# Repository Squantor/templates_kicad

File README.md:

# kicad_templates
Kicad templates that I use regularly
## checkout notes
This repository contains a few submodules, so after checking out do not forget to also check out the submodules.
```
git clone https://github.com/Squantor/LPC-breakout-boards.git
git submodule init
git submodule update
```
Submodules are my private kicad library that are used in my projects. I do try to use the kicad components as much as possible but for certain component types they are less then optimal or they do not exist.

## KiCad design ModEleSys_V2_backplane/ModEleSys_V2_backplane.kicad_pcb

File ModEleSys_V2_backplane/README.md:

# 10 by 10 cm aluminium box backplane
10 by 10 cm aluminium box backplane  capable of fitting 4 5*4cm modules
## TODO's
Still some things need to be done:
* Fill in this project description
* schematic entry 
* PCB layout
* Review with one night in between
* Production
* Assemble
* Test & characterise
* update Readme.md with pictures and BOM
## BOM
This is a list of hardware components. If just mentioned a generic component like a 1K 0402 resistor, just name it as such, free to substitute. If you need some special integrated IC's show some sources like Mouser, Digikey, Farnell, or LCSC
* Search on ebay/aliexpress for a 10 by 10 by 5 extruded aluminium box.
* Generic resistor in 0402 housing with a value
* Generic capacitor in 0603 housing with a value
* Special IC from [LCSC](https://lcsc.com/)
## Pictures

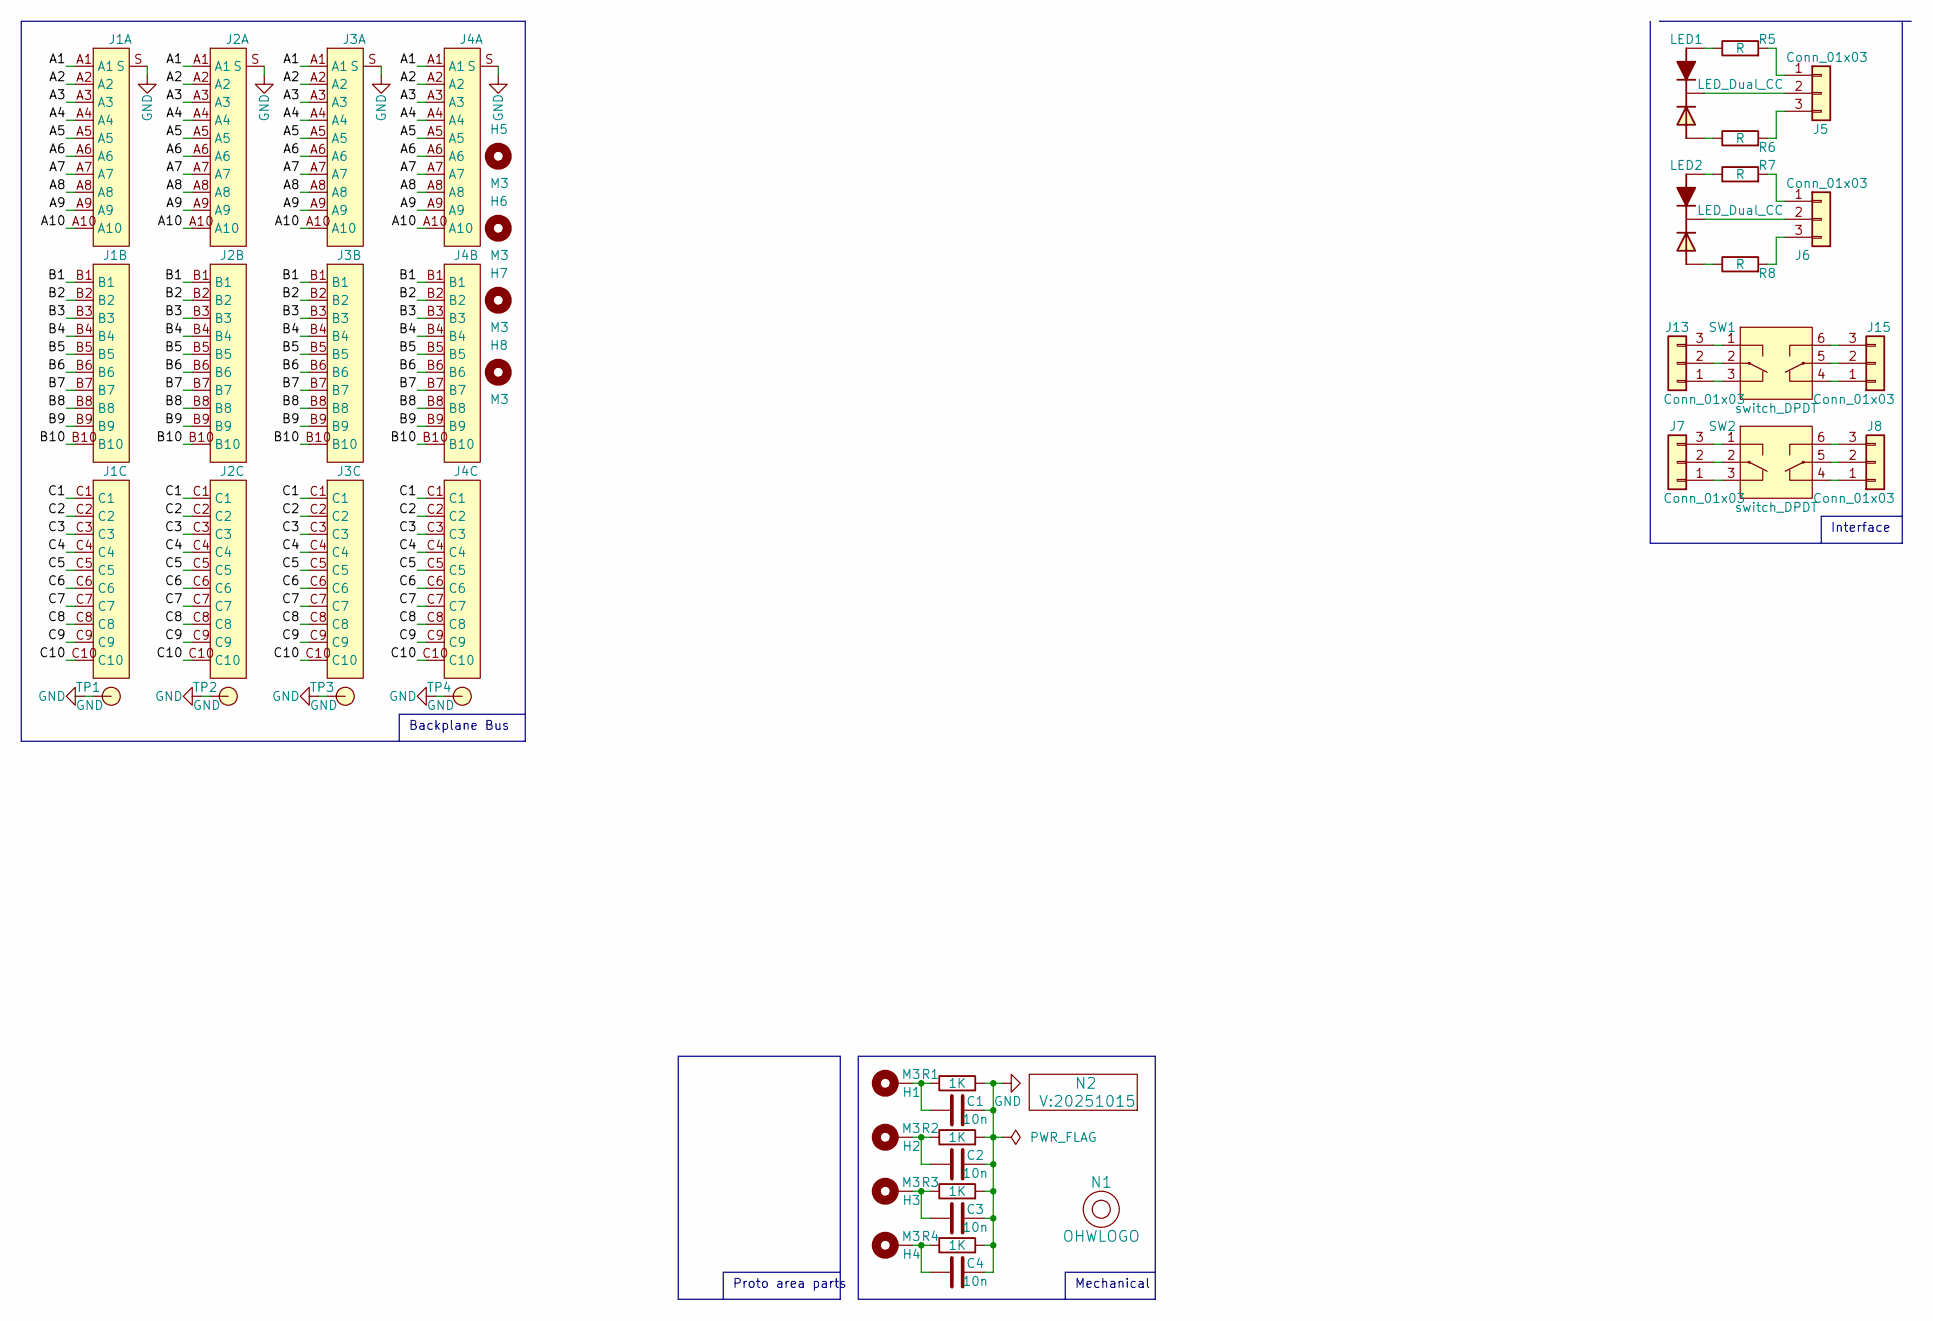
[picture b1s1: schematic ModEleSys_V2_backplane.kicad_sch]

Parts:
C1, C2, C3, C4: 10n; C_0805+0603
H1, H2, H3, H4, H5, H6, H7, H8: M3; MountingHole_3.2mm_M3_Pad_Via
J1, J2, J3, J4: DIN41612_C3_3x10_Female_Vertical_THT_shields
J5, J6, J7, J8, J13, J15: Conn_01x03; JST_PH_B3B-PH-K_1x03_P2.00mm_Vertical
LED1, LED2: LED_Dual_CC; LED_DUAL_TH245_90deg
N1: OHWLOGO; OSHW-Symbol_6.7x6mm_SilkScreen
N2: V:20251015; Label_Generic
R1, R2, R3, R4: 1K; R_0805+0603
R5, R6, R7, R8: R; R_0603_hand
SW1, SW2: switch_DPDT; PS-22F02
TP1, TP2, TP3, TP4: GND; TestPoint_hole_H05R10

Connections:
/A1: J1.A1, J2.A1, J3.A1, J4.A1
/A2: J1.A2, J2.A2, J3.A2, J4.A2
/A3: J1.A3, J2.A3, J3.A3, J4.A3
/A4: J1.A4, J2.A4, J3.A4, J4.A4
/A5: J1.A5, J2.A5, J3.A5, J4.A5
/A6: J1.A6, J2.A6, J3.A6, J4.A6
/A7: J1.A7, J2.A7, J3.A7, J4.A7
/A8: J1.A8, J2.A8, J3.A8, J4.A8
/A9: J1.A9, J2.A9, J3.A9, J4.A9
/A10: J1.A10, J2.A10, J3.A10, J4.A10
/B1: J1.B1, J2.B1, J3.B1, J4.B1
/B2: J1.B2, J2.B2, J3.B2, J4.B2
/B3: J1.B3, J2.B3, J3.B3, J4.B3
/B4: J1.B4, J2.B4, J3.B4, J4.B4
/B5: J1.B5, J2.B5, J3.B5, J4.B5
/B6: J1.B6, J2.B6, J3.B6, J4.B6
/B7: J1.B7, J2.B7, J3.B7, J4.B7
/B8: J1.B8, J2.B8, J3.B8, J4.B8
/B9: J1.B9, J2.B9, J3.B9, J4.B9
/B10: J1.B10, J2.B10, J3.B10, J4.B10
/C1: J1.C1, J2.C1, J3.C1, J4.C1
/C2: J1.C2, J2.C2, J3.C2, J4.C2
/C3: J1.C3, J2.C3, J3.C3, J4.C3
/C4: J1.C4, J2.C4, J3.C4, J4.C4
/C5: J1.C5, J2.C5, J3.C5, J4.C5
/C6: J1.C6, J2.C6, J3.C6, J4.C6
/C7: J1.C7, J2.C7, J3.C7, J4.C7
/C8: J1.C8, J2.C8, J3.C8, J4.C8
/C9: J1.C9, J2.C9, J3.C9, J4.C9
/C10: J1.C10, J2.C10, J3.C10, J4.C10
GND: C1.2, C2.2, C3.2, C4.2, J1.S, J2.S, J3.S, J4.S, R1.2, R2.2, R3.2, R4.2, TP1.1, TP2.1, TP3.1, TP4.1
unnamed: C1.1, H1.1, R1.1
unnamed: C2.1, H2.1, R2.1
unnamed: C3.1, H3.1, R3.1
unnamed: C4.1, H4.1, R4.1
unnamed: J5.1, R5.2
unnamed: J5.2, LED1.2 (C)
unnamed: J5.3, R6.2
unnamed: J6.1, R7.2
unnamed: J6.2, LED2.2 (C)
unnamed: J6.3, R8.2
unnamed: J7.1, SW2.3 (SW1_P2)
unnamed: J7.2, SW2.2 (SW1_C1)
unnamed: J7.3, SW2.1 (SW1_P1)
unnamed: J8.1, SW2.4 (SW2_P2)
unnamed: J8.2, SW2.5 (SW2_C1)
unnamed: J8.3, SW2.6 (SW2_P2)
unnamed: J13.1, SW1.3 (SW1_P2)
unnamed: J13.2, SW1.2 (SW1_C1)
unnamed: J13.3, SW1.1 (SW1_P1)
unnamed: J15.1, SW1.4 (SW2_P2)
unnamed: J15.2, SW1.5 (SW2_C1)
unnamed: J15.3, SW1.6 (SW2_P2)
unnamed: LED1.1 (A1), R5.1
unnamed: LED1.3 (A2), R6.1
unnamed: LED2.1 (A1), R7.1
unnamed: LED2.3 (A2), R8.1

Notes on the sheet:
Proto area parts
Mechanical
Interface
Backplane Bus

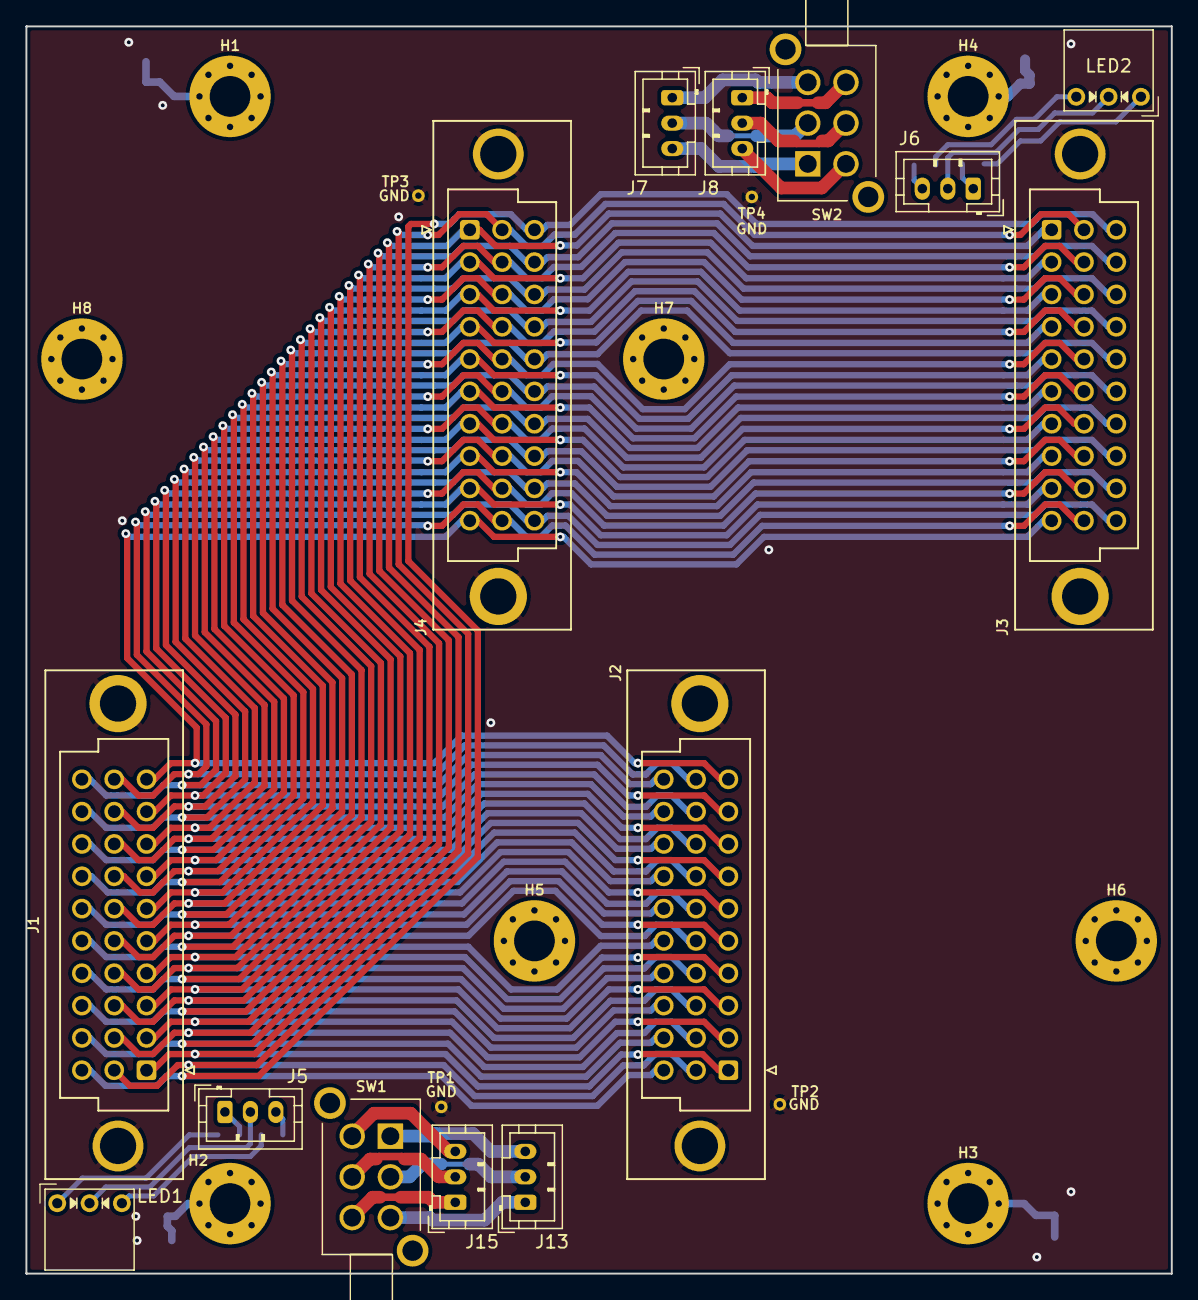
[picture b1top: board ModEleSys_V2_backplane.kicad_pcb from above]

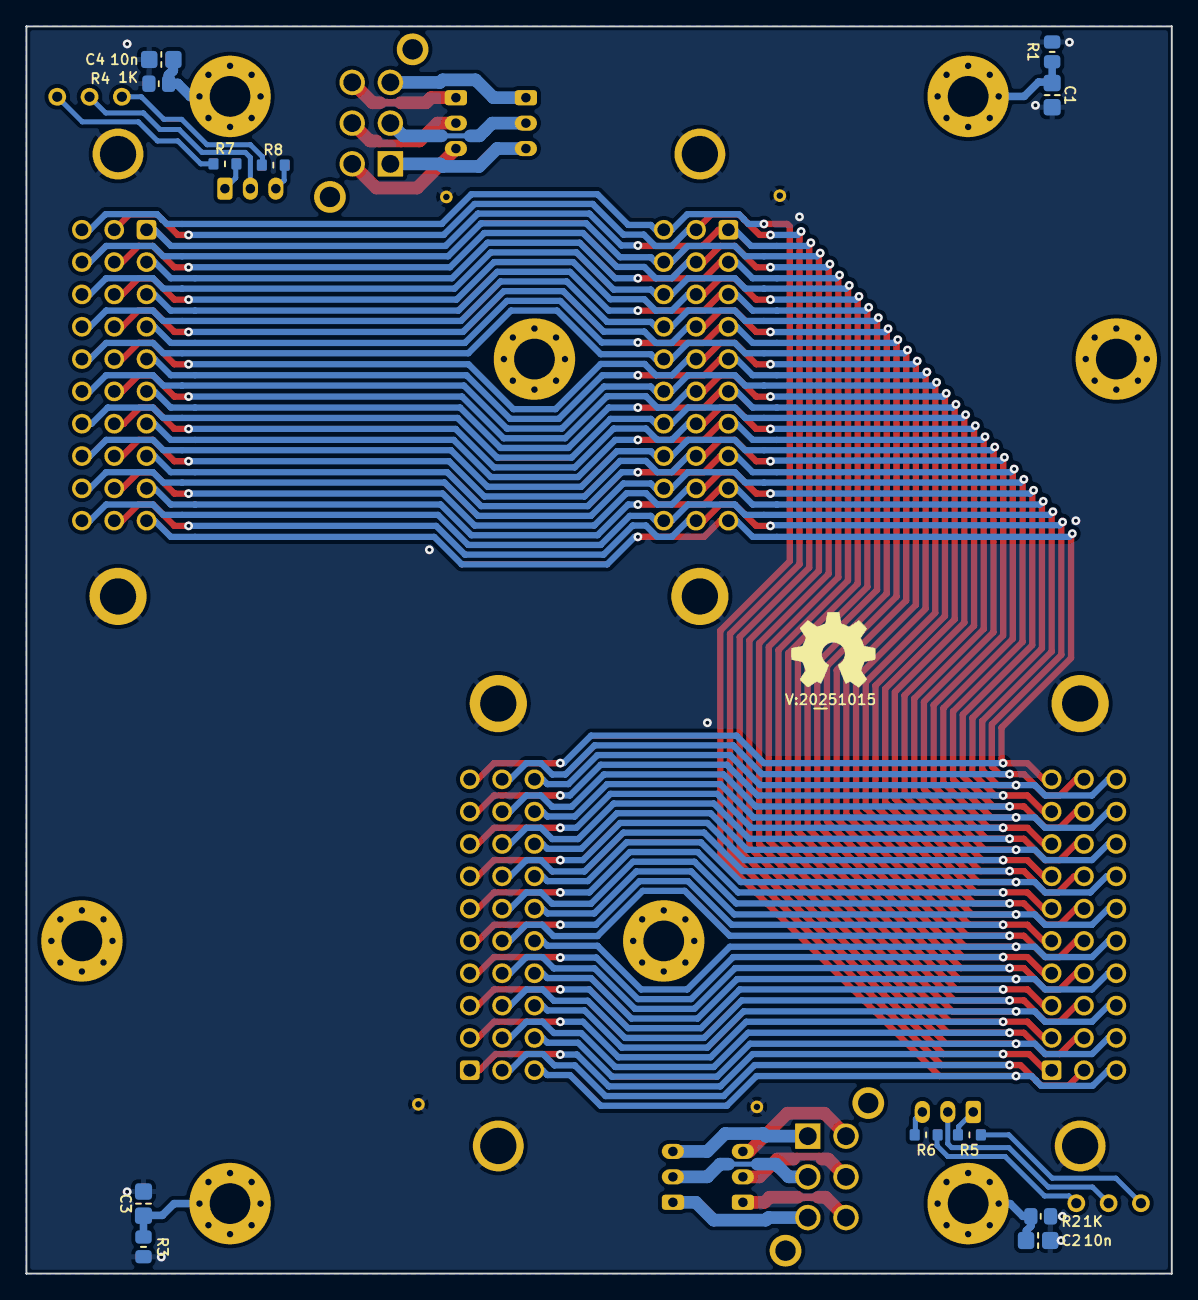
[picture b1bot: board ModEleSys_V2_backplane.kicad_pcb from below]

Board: 2 copper layers, 90.0 x 98.0 mm, 40 parts (14 on the bottom side), 57 nets.

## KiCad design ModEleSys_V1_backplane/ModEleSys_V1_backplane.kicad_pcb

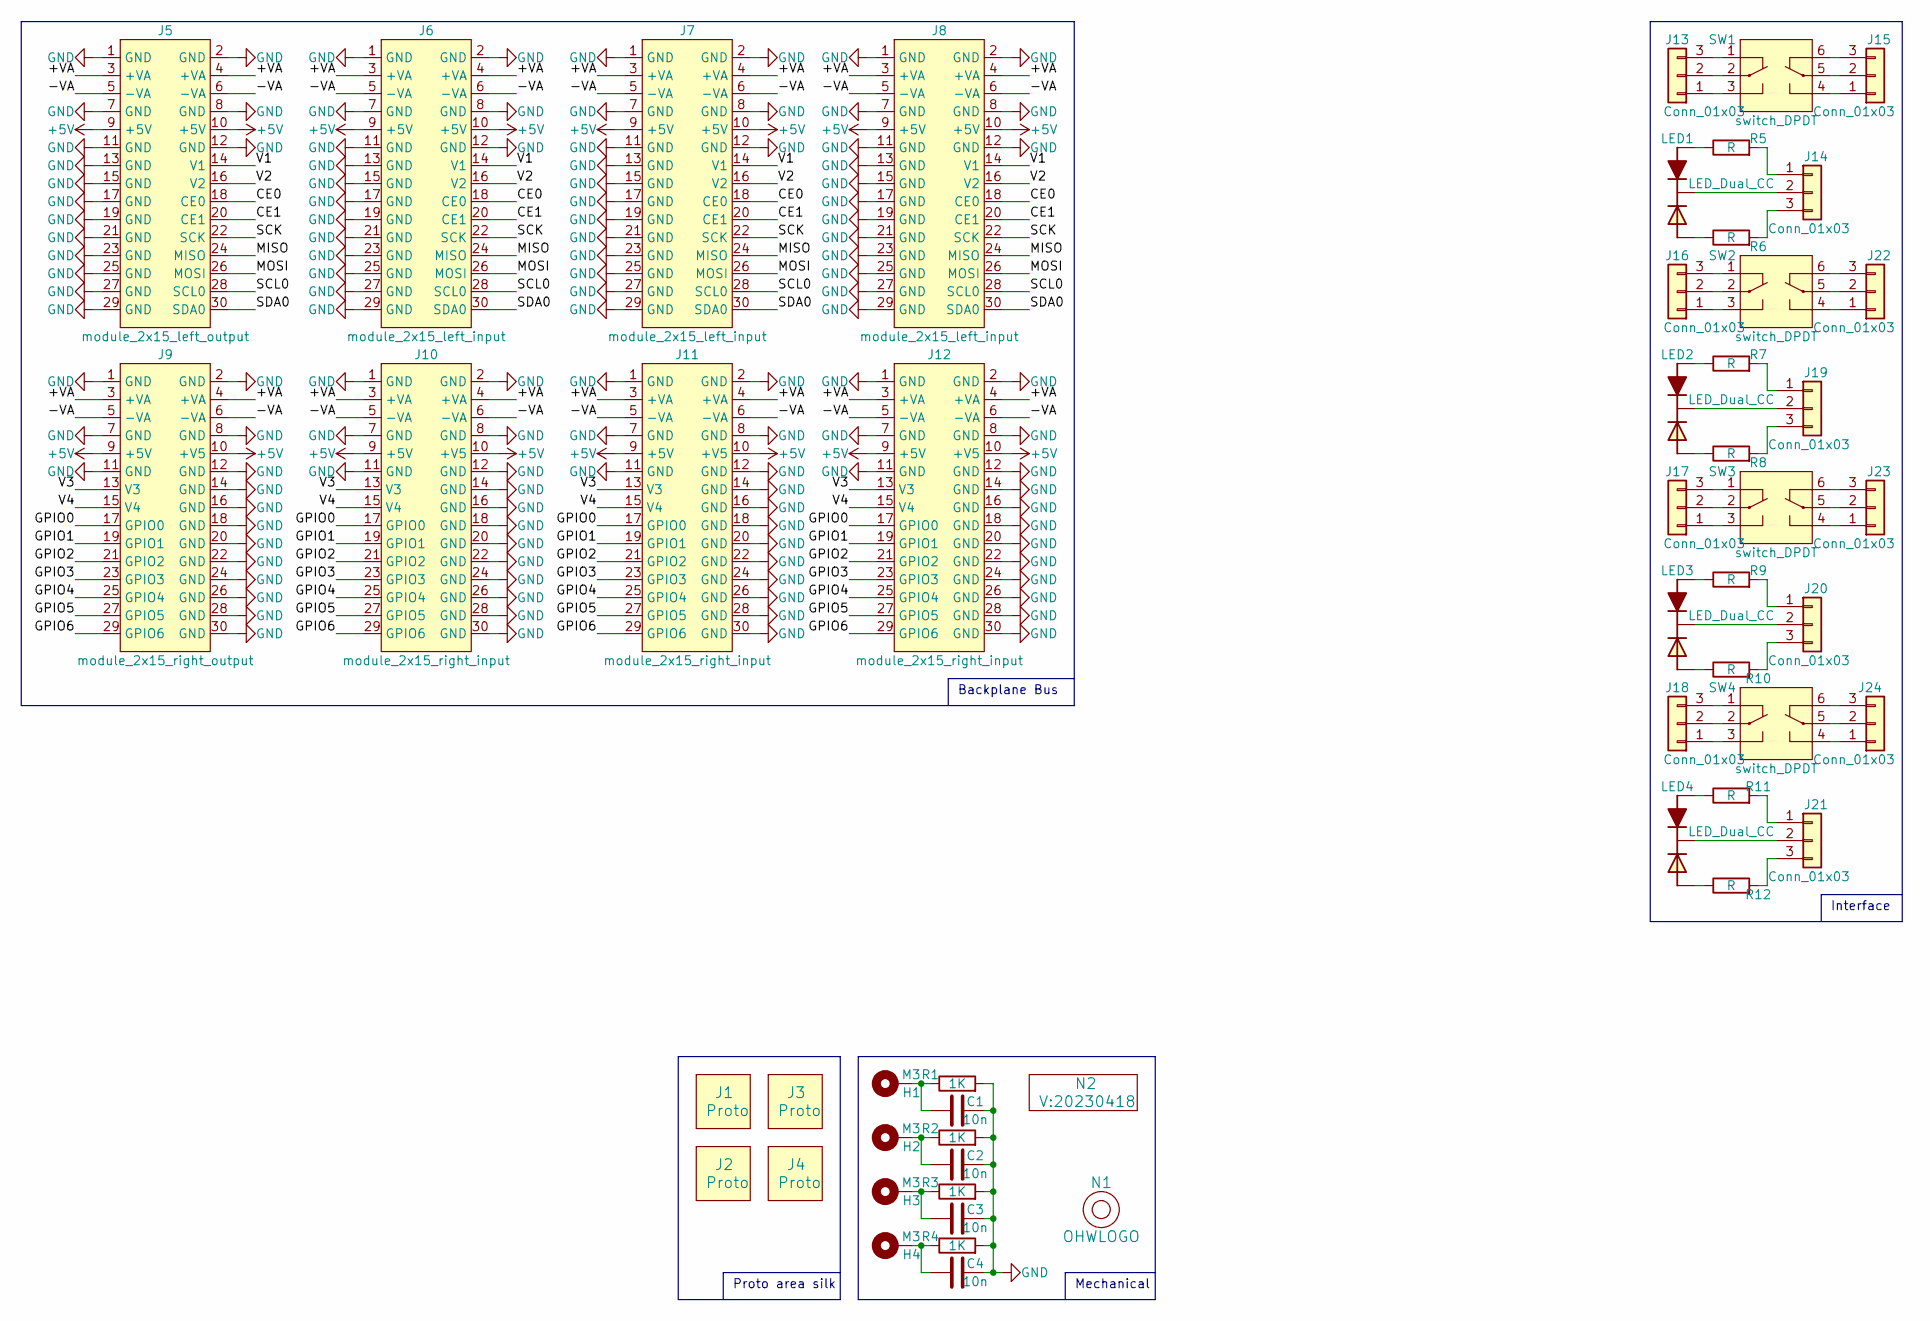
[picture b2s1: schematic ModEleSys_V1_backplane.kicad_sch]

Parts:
C1, C2, C3, C4: 10n; C_0805+0603
H1, H2, H3, H4: M3; MountingHole_3.2mm_M3_Pad_Via
J1, J2, J3, J4: Proto; 4by4cm_module
J5: module_2x15_left_output; module_2x15_left
J6, J7, J8: module_2x15_left_input; module_2x15_left
J9: module_2x15_right_output; module_2x15_right
J10, J11, J12: module_2x15_right_input; module_2x15_right
J13, J14, J15, J16, J17, J18, J19, J20, J21, J22, J23, J24: Conn_01x03; JST_PH_B3B-PH-K_1x03_P2.00mm_Vertical
LED1, LED2, LED3, LED4: LED_Dual_CC; LED_DUAL_TH245_90deg
N1: OHWLOGO; OSHW-Symbol_6.7x6mm_SilkScreen
N2: V:20230418; Label_Generic
R1, R2, R3, R4: 1K; R_0805+0603
R5, R6, R7, R8, R9, R10, R11, R12: R; R_0603_hand
SW1, SW2, SW3, SW4: switch_DPDT; PS-22F02

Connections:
+5V: J5.9 (+5V), J5.10 (+5V), J6.9 (+5V), J6.10 (+5V), J7.9 (+5V), J7.10 (+5V), J8.9 (+5V), J8.10 (+5V), J9.9 (+5V), J9.10 (+V5), J10.9 (+5V), J10.10 (+V5), J11.9 (+5V), J11.10 (+V5), J12.9 (+5V), J12.10 (+V5)
/+VA: J5.3 (+VA), J5.4 (+VA), J6.3 (+VA), J6.4 (+VA), J7.3 (+VA), J7.4 (+VA), J8.3 (+VA), J8.4 (+VA), J9.3 (+VA), J9.4 (+VA), J10.3 (+VA), J10.4 (+VA), J11.3 (+VA), J11.4 (+VA), J12.3 (+VA), J12.4 (+VA)
/-VA: J5.5 (-VA), J5.6 (-VA), J6.5 (-VA), J6.6 (-VA), J7.5 (-VA), J7.6 (-VA), J8.5 (-VA), J8.6 (-VA), J9.5 (-VA), J9.6 (-VA), J10.5 (-VA), J10.6 (-VA), J11.5 (-VA), J11.6 (-VA), J12.5 (-VA), J12.6 (-VA)
/CE0: J5.18 (CE0), J6.18 (CE0), J7.18 (CE0), J8.18 (CE0)
/CE1: J5.20 (CE1), J6.20 (CE1), J7.20 (CE1), J8.20 (CE1)
/GPIO0: J9.17 (GPIO0), J10.17 (GPIO0), J11.17 (GPIO0), J12.17 (GPIO0)
/GPIO1: J9.19 (GPIO1), J10.19 (GPIO1), J11.19 (GPIO1), J12.19 (GPIO1)
/GPIO2: J9.21 (GPIO2), J10.21 (GPIO2), J11.21 (GPIO2), J12.21 (GPIO2)
/GPIO3: J9.23 (GPIO3), J10.23 (GPIO3), J11.23 (GPIO3), J12.23 (GPIO3)
/GPIO4: J9.25 (GPIO4), J10.25 (GPIO4), J11.25 (GPIO4), J12.25 (GPIO4)
/GPIO5: J9.27 (GPIO5), J10.27 (GPIO5), J11.27 (GPIO5), J12.27 (GPIO5)
/GPIO6: J9.29 (GPIO6), J10.29 (GPIO6), J11.29 (GPIO6), J12.29 (GPIO6)
/MISO: J5.24 (MISO), J6.24 (MISO), J7.24 (MISO), J8.24 (MISO)
/MOSI: J5.26 (MOSI), J6.26 (MOSI), J7.26 (MOSI), J8.26 (MOSI)
/SCK: J5.22 (SCK), J6.22 (SCK), J7.22 (SCK), J8.22 (SCK)
/SCL0: J5.28 (SCL0), J6.28 (SCL0), J7.28 (SCL0), J8.28 (SCL0)
/SDA0: J5.30 (SDA0), J6.30 (SDA0), J7.30 (SDA0), J8.30 (SDA0)
/V1: J5.14 (V1), J6.14 (V1), J7.14 (V1), J8.14 (V1)
/V2: J5.16 (V2), J6.16 (V2), J7.16 (V2), J8.16 (V2)
/V3: J9.13 (V3), J10.13 (V3), J11.13 (V3), J12.13 (V3)
/V4: J9.15 (V4), J10.15 (V4), J11.15 (V4), J12.15 (V4)
GND: C1.2, C2.2, C3.2, C4.2, J5.1 (GND), J5.2 (GND), J5.7 (GND), J5.8 (GND), J5.11 (GND), J5.12 (GND), J5.13 (GND), J5.15 (GND), J5.17 (GND), J5.19 (GND), J5.21 (GND), J5.23 (GND), J5.25 (GND), J5.27 (GND), J5.29 (GND), J6.1 (GND), J6.2 (GND), J6.7 (GND), J6.8 (GND), J6.11 (GND), J6.12 (GND), J6.13 (GND), J6.15 (GND), J6.17 (GND), J6.19 (GND), J6.21 (GND), J6.23 (GND), J6.25 (GND), J6.27 (GND), J6.29 (GND), J7.1 (GND), J7.2 (GND), J7.7 (GND), J7.8 (GND), J7.11 (GND), J7.12 (GND), J7.13 (GND), J7.15 (GND), J7.17 (GND), J7.19 (GND), J7.21 (GND), J7.23 (GND), J7.25 (GND), J7.27 (GND), J7.29 (GND), J8.1 (GND), J8.2 (GND), J8.7 (GND), J8.8 (GND), J8.11 (GND), J8.12 (GND), J8.13 (GND), J8.15 (GND), J8.17 (GND), J8.19 (GND), J8.21 (GND), J8.23 (GND), J8.25 (GND), J8.27 (GND), J8.29 (GND), J9.1 (GND), J9.2 (GND), J9.7 (GND), J9.8 (GND), J9.11 (GND), J9.12 (GND), J9.14 (GND), J9.16 (GND), J9.18 (GND), J9.20 (GND), J9.22 (GND), J9.24 (GND), J9.26 (GND), J9.28 (GND), J9.30 (GND), J10.1 (GND), J10.2 (GND), J10.7 (GND), J10.8 (GND), J10.11 (GND), J10.12 (GND), J10.14 (GND), J10.16 (GND), J10.18 (GND), J10.20 (GND), J10.22 (GND), J10.24 (GND), J10.26 (GND), J10.28 (GND), J10.30 (GND), J11.1 (GND), J11.2 (GND), J11.7 (GND), J11.8 (GND), J11.11 (GND), J11.12 (GND), J11.14 (GND), J11.16 (GND), J11.18 (GND), J11.20 (GND), J11.22 (GND), J11.24 (GND), J11.26 (GND), J11.28 (GND), J11.30 (GND), J12.1 (GND), J12.2 (GND), J12.7 (GND), J12.8 (GND), J12.11 (GND), J12.12 (GND), J12.14 (GND), J12.16 (GND), J12.18 (GND), J12.20 (GND), J12.22 (GND), J12.24 (GND), J12.26 (GND), J12.28 (GND), J12.30 (GND), R1.2, R2.2, R3.2, R4.2
unnamed: C1.1, H1.1, R1.1
unnamed: C2.1, H2.1, R2.1
unnamed: C3.1, H3.1, R3.1
unnamed: C4.1, H4.1, R4.1
unnamed: J13.1, SW1.3 (SW1_P2)
unnamed: J13.2, SW1.2 (SW1_C1)
unnamed: J13.3, SW1.1 (SW1_P1)
unnamed: J14.1, R5.2
unnamed: J14.2, LED1.2 (C)
unnamed: J14.3, R6.2
unnamed: J15.1, SW1.4 (SW2_P2)
unnamed: J15.2, SW1.5 (SW2_C1)
unnamed: J15.3, SW1.6 (SW2_P2)
unnamed: J16.1, SW2.3 (SW1_P2)
unnamed: J16.2, SW2.2 (SW1_C1)
unnamed: J16.3, SW2.1 (SW1_P1)
unnamed: J17.1, SW3.3 (SW1_P2)
unnamed: J17.2, SW3.2 (SW1_C1)
unnamed: J17.3, SW3.1 (SW1_P1)
unnamed: J18.1, SW4.3 (SW1_P2)
unnamed: J18.2, SW4.2 (SW1_C1)
unnamed: J18.3, SW4.1 (SW1_P1)
unnamed: J19.1, R7.2
unnamed: J19.2, LED2.2 (C)
unnamed: J19.3, R8.2
unnamed: J20.1, R9.2
unnamed: J20.2, LED3.2 (C)
unnamed: J20.3, R10.2
unnamed: J21.1, R11.2
unnamed: J21.2, LED4.2 (C)
unnamed: J21.3, R12.2
unnamed: J22.1, SW2.4 (SW2_P2)
unnamed: J22.2, SW2.5 (SW2_C1)
unnamed: J22.3, SW2.6 (SW2_P2)
unnamed: J23.1, SW3.4 (SW2_P2)
unnamed: J23.2, SW3.5 (SW2_C1)
unnamed: J23.3, SW3.6 (SW2_P2)
unnamed: J24.1, SW4.4 (SW2_P2)
unnamed: J24.2, SW4.5 (SW2_C1)
unnamed: J24.3, SW4.6 (SW2_P2)
unnamed: LED1.1 (A1), R5.1
unnamed: LED1.3 (A2), R6.1
unnamed: LED2.1 (A1), R7.1
unnamed: LED2.3 (A2), R8.1
unnamed: LED3.1 (A1), R9.1
unnamed: LED3.3 (A2), R10.1
unnamed: LED4.1 (A1), R11.1
unnamed: LED4.3 (A2), R12.1

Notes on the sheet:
Proto area silk
Interface
Mechanical
Backplane Bus

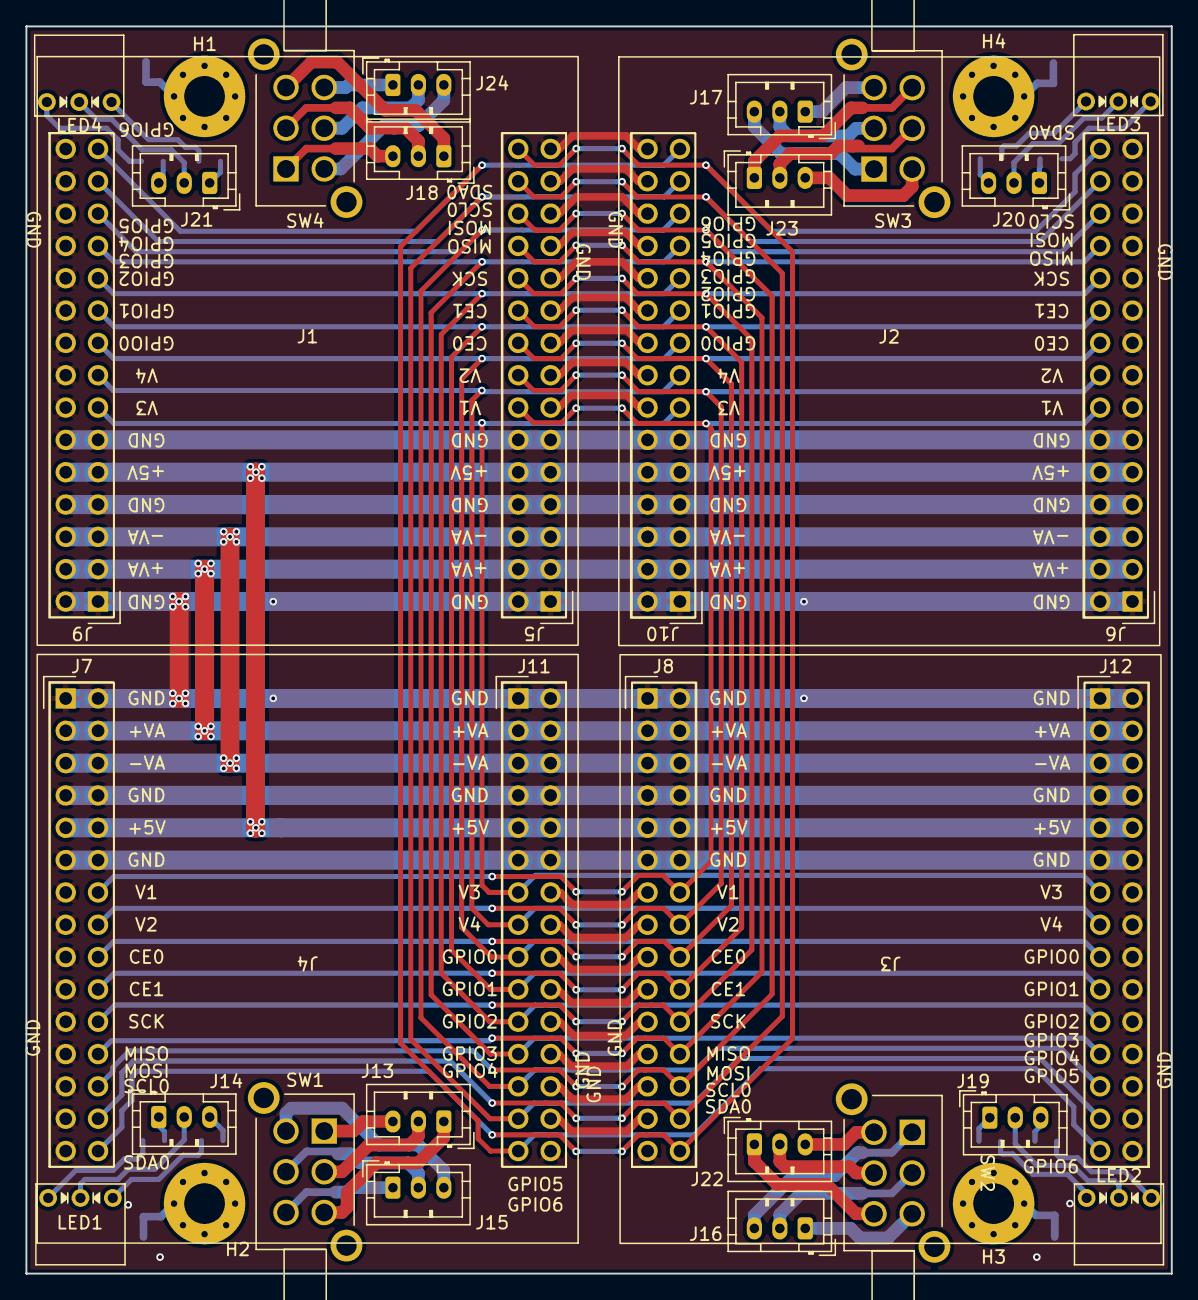
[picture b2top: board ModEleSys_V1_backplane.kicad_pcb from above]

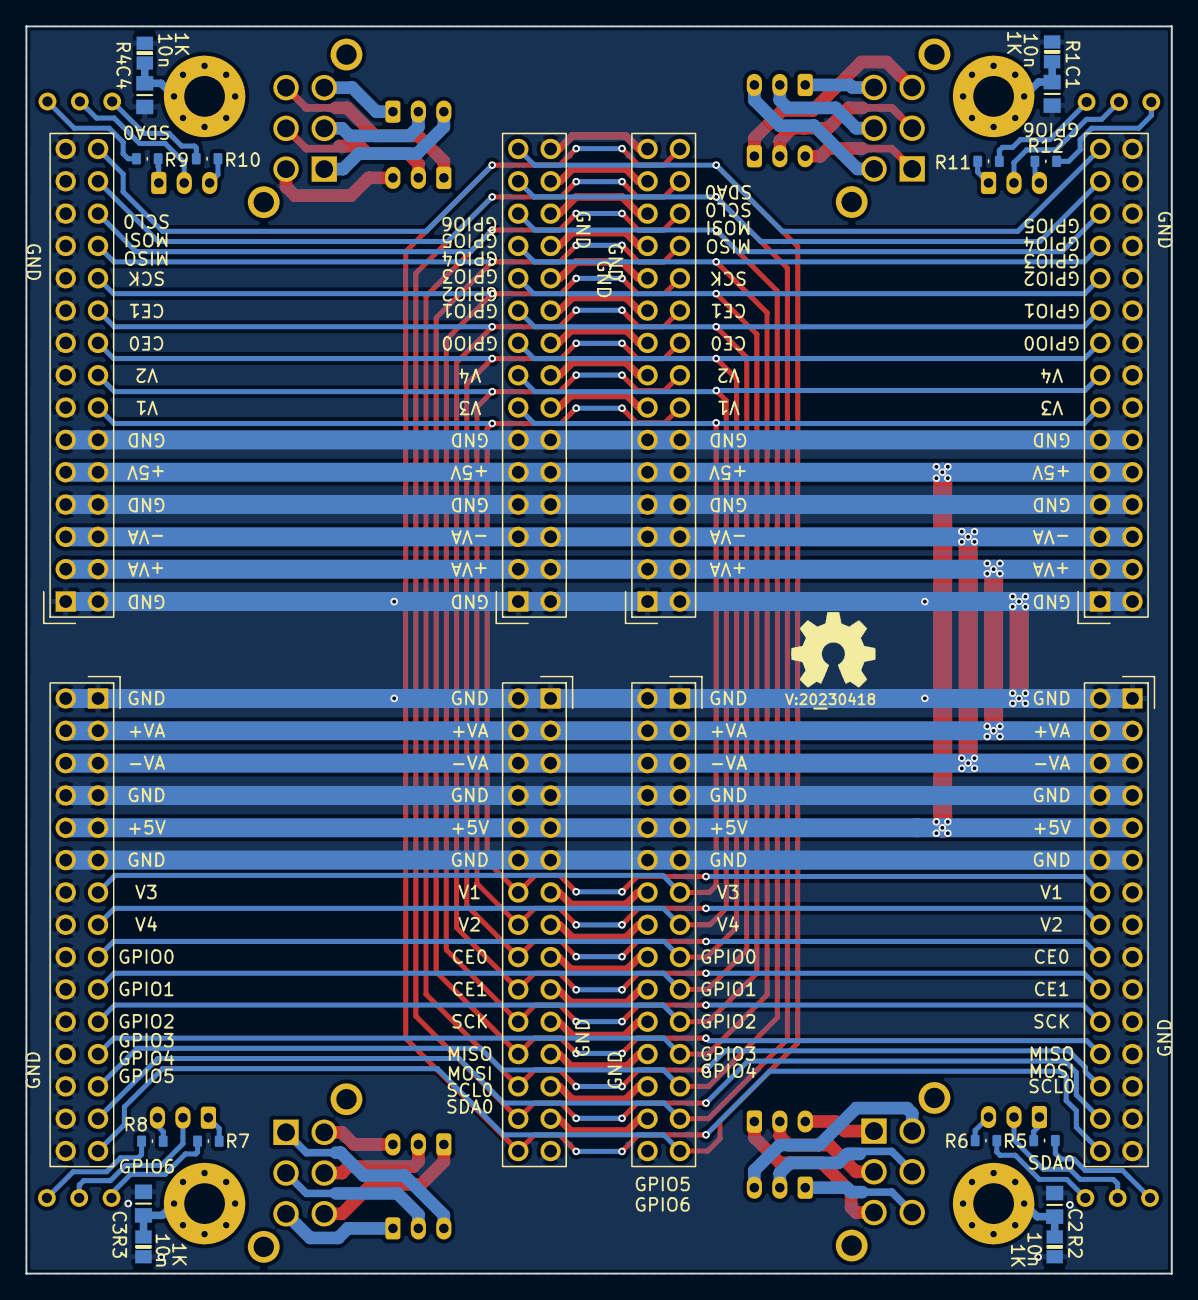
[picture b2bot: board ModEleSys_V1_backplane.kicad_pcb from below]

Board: 2 copper layers, 90.0 x 98.0 mm, 54 parts (18 on the bottom side), 70 nets.

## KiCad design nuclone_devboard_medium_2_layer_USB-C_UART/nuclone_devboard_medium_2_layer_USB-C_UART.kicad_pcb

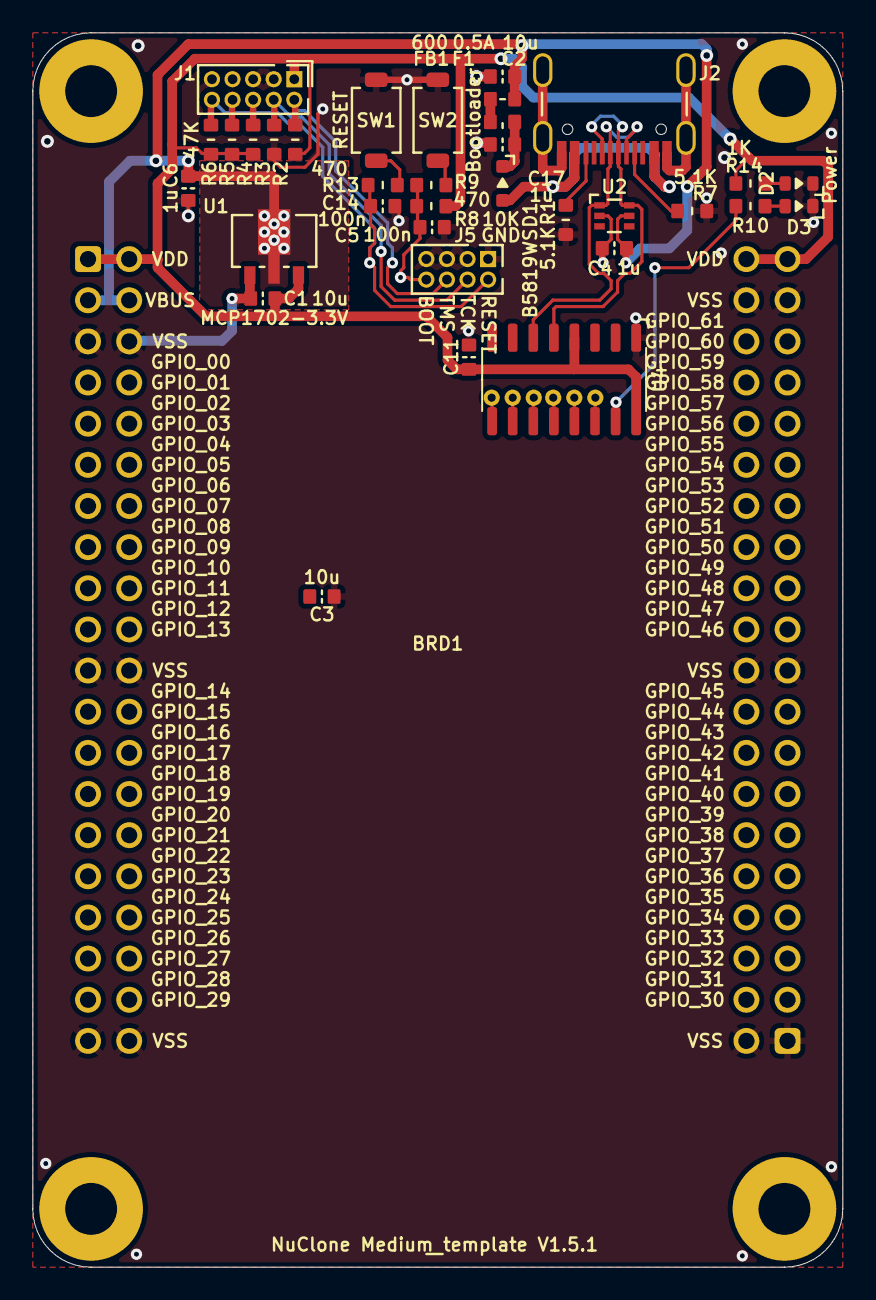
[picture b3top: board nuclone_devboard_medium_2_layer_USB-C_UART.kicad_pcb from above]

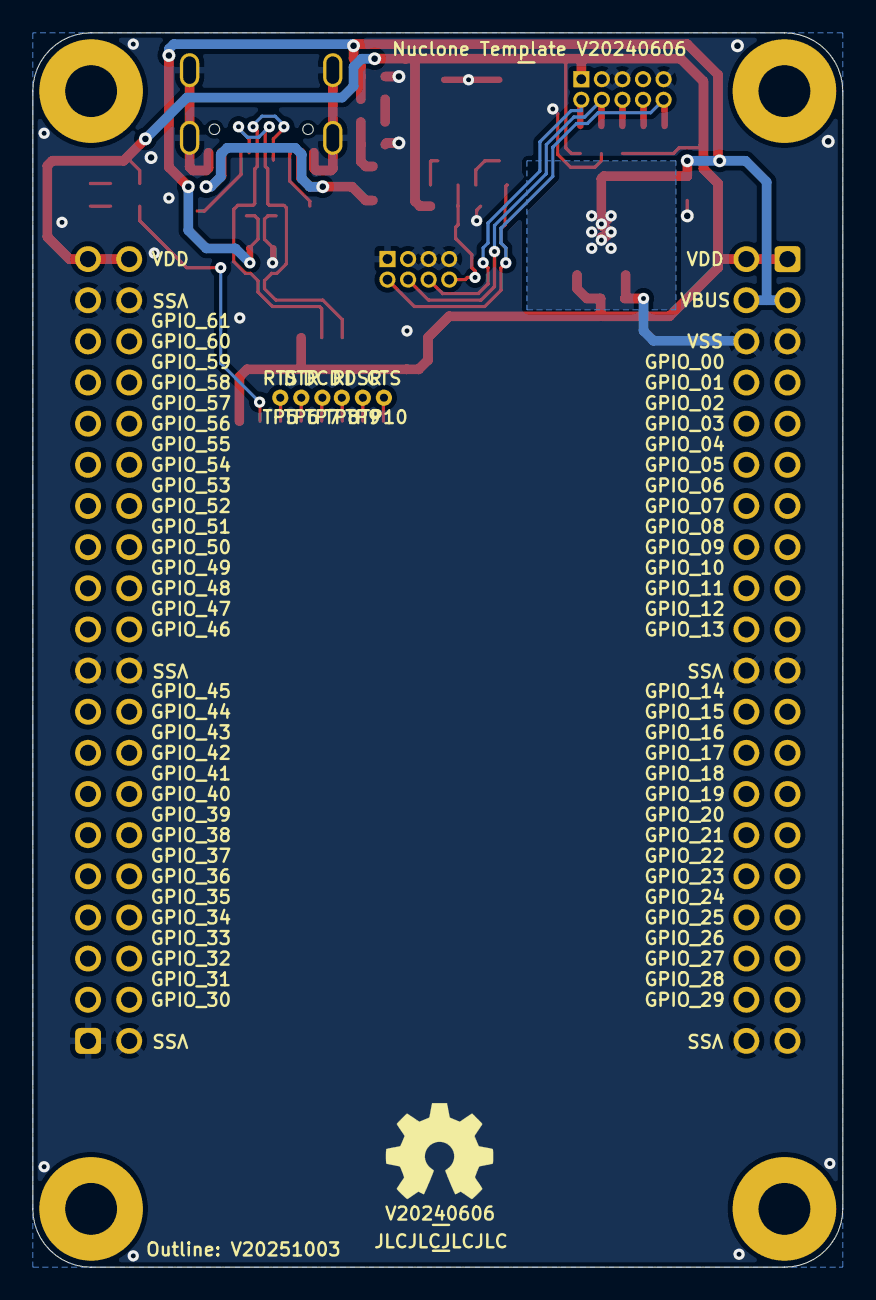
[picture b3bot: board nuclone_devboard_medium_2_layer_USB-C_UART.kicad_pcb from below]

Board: 2 copper layers, 50.0 x 76.2 mm, 46 parts (10 on the bottom side), 27 nets.

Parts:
BRD1: Devboard_medium_generic
C1, C2, C3, C11: 10u; C_0603
C4, C6, C17: 1u; C_0603
C5, C14: 100n; C_0603
D1: B5819WS; SOD-323-nexperia-hand
D2: GREEN; LED_0603_hand
D3: RED; LED_0603_hand
F1: 0.5A; F_0603_hand
FB1: 600; L_0603
J1: JTAG_2X05; Header-0127-2X05-H006
J2: TYPE-C-31-M-12; USB-C-HRO-31-M-12_aisler
J5: Conn_02x06_Odd_Even; Header-0127-2X04-H006
N1: OHWLOGO; OSHW-Symbol_6.7x6mm_SilkScreen
N2: V20240606; Label_Generic
N3: JLCJLCJLCJLC; Label_Generic
N4: NuClone Medium template V1.5.1; Label_Generic
N5: Nuclone Template V20240606; Label_Generic
R1, R7: 5.1K; R_0603_hand
R2, R3, R4, R5, R6: 47K; R_0603_hand
R8: 10K; R_0603_hand
R9, R13: 470; R_0603_hand
R10, R14: 1K; R_0603_hand
SW1: RESET; TD-85XU
SW2: Bootloader; TD-85XU
TP5: RTS; TestPoint_hole_H05R10
TP6: DTR; TestPoint_hole_H05R10
TP7: DCD; TestPoint_hole_H05R10
TP8: RI; TestPoint_hole_H05R10
TP9: DSR; TestPoint_hole_H05R10
TP10: CTS; TestPoint_hole_H05R10
U1: MCP1702-3.3V; SOT89-NXP
U2: TPESD0504C6; SOT363-ONsemi
U4: CH340B; SOIC-16_3.9x9.9mm_P1.27mm

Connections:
/BOOT: C5.1, J5.8, R8.1, R9.1
/DN: J2.A7 (DN1), J2.B7 (DN2), U2.1 (IO_1), U4.6 (UD-)
/DP: J2.A6 (DP1), J2.B6 (DP2), U2.6 (IO_4), U4.5 (UD+)
/RESET: C14.2, J1.10 (nRESET), J5.2, R6.1, R13.1
/TCK: J1.4 (SWDCLK/TCK), J5.4, R3.1
/TDI: J1.8 (TDI), R5.1
/TDO: J1.6 (SWO/TDO), R4.1
/TMS: J1.2 (SWDIO/TMS), J5.6, R2.1
/TNOW: R10.2, U4.15 (TNOW)
/VBUS: BRD1.3 (VBUS), BRD1.4 (VBUS), C2.2, C4.1, C6.2, F1.1, U1.2 (Vin), U2.5 (VDD)
/VDD: BRD1.1 (VDD), BRD1.2 (VDD), BRD1.79 (VDD), BRD1.80 (VDD), C1.1, C3.2, C11.1, J1.1 (VCC), R2.2, R4.2, R5.2, R6.2, R8.2, R14.2, U1.3 (Vout), U4.4 (V3), U4.16 (VCC)
/VSS: BRD1.5 (VSS), BRD1.6 (VSS), BRD1.21 (VSS), BRD1.22 (VSS), BRD1.39 (VSS), BRD1.40 (VSS), BRD1.41 (VSS), BRD1.42 (VSS), BRD1.59 (VSS), BRD1.60 (VSS), BRD1.77 (VSS), BRD1.78 (VSS), C1.2, C2.1, C3.1, C4.2, C5.2, C6.1, C11.2, C14.1, C17.1, D2.1 (K), D3.1 (K), J1.3 (GND), J1.5 (GND), J1.9 (GNDDET), J2.A1B12 (GND), J2.B1A12 (GND), J2.S (Shield), J5.1, J5.3, J5.5, J5.7, R1.1, R3.2, R7.1, SW1.1, SW2.1, U1.1 (GND), U2.2 (VSS), U4.1 (GND)
unnamed: D1.2 (A), J2.A4B9 (VBUS), J2.B4A9 (VBUS)
unnamed: C17.2, D1.1 (K), FB1.2
unnamed: D2.2 (A), R14.1
unnamed: D3.2 (A), R10.1
unnamed: F1.2, FB1.1
unnamed: J2.A5 (CC1), R7.2
unnamed: J2.B5 (CC2), R1.2
unnamed: R9.2, SW2.2
unnamed: R13.2, SW1.2
unnamed: TP10.1, U4.9 (CTS#)
unnamed: TP7.1, U4.12 (DCD#)
unnamed: TP9.1, U4.10 (DSR#)
unnamed: TP6.1, U4.13 (DTR#)
unnamed: TP8.1, U4.11 (RI#)
unnamed: TP5.1, U4.14 (RTS#)

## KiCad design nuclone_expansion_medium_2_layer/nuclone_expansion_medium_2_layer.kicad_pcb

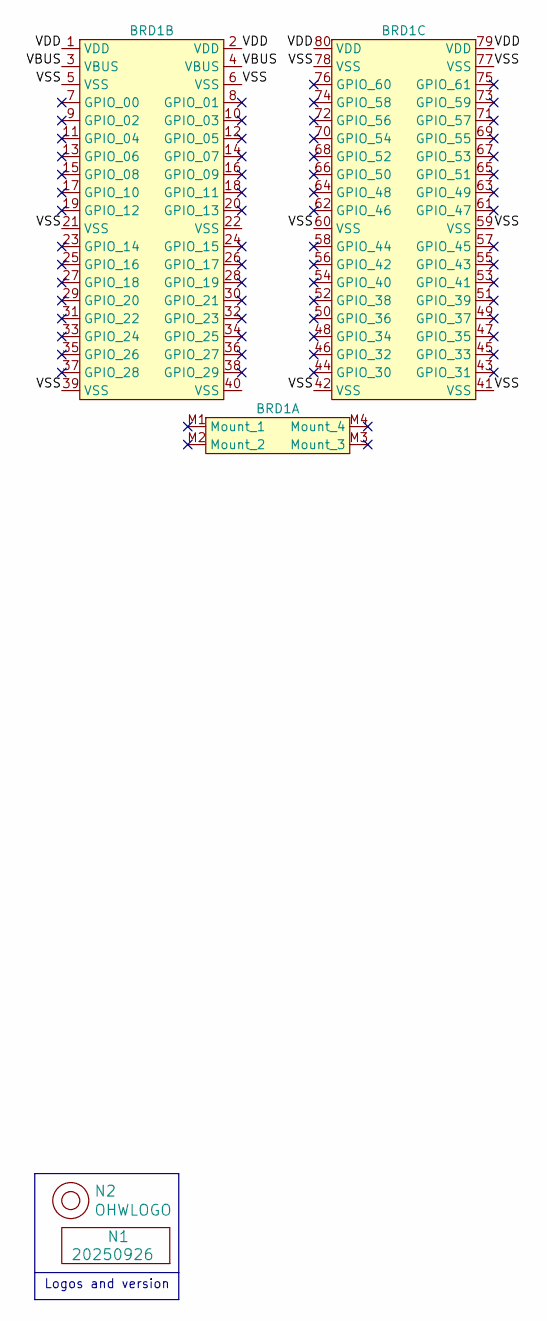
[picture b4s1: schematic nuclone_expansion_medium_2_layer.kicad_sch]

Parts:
BRD1: expansion_medium_generic
N1: 20250926; Label_Generic
N2: OHWLOGO; OSHW-Symbol_6.7x6mm_SilkScreen

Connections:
/VBUS: BRD1.3 (VBUS), BRD1.4 (VBUS)
/VDD: BRD1.1 (VDD), BRD1.2 (VDD), BRD1.79 (VDD), BRD1.80 (VDD)
/VSS: BRD1.5 (VSS), BRD1.6 (VSS), BRD1.21 (VSS), BRD1.39 (VSS), BRD1.41 (VSS), BRD1.42 (VSS), BRD1.59 (VSS), BRD1.60 (VSS), BRD1.77 (VSS), BRD1.78 (VSS)

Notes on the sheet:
Logos and version
